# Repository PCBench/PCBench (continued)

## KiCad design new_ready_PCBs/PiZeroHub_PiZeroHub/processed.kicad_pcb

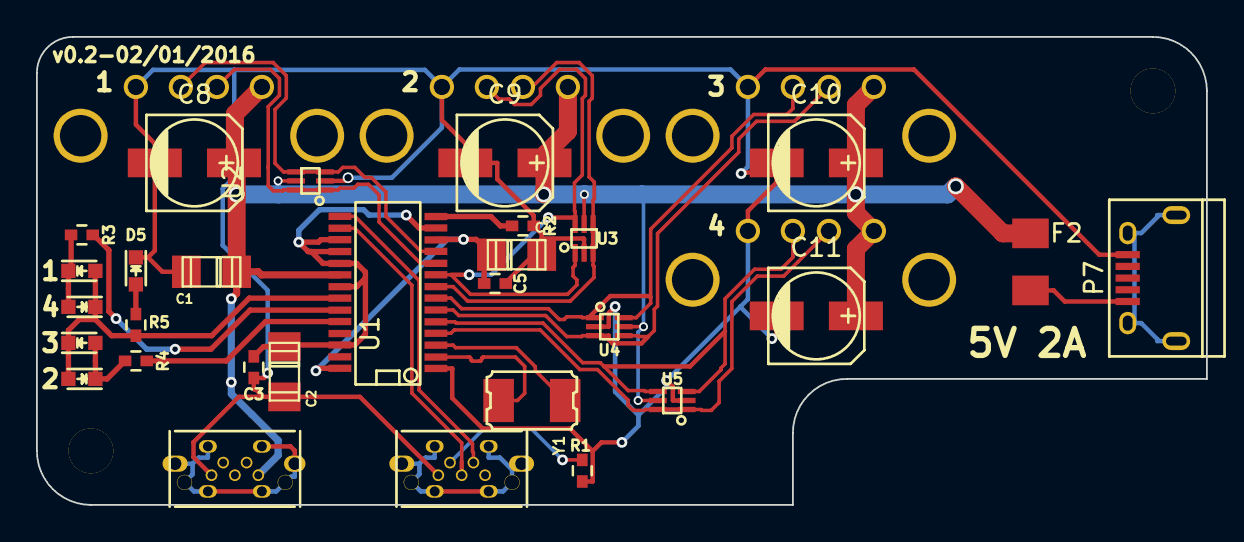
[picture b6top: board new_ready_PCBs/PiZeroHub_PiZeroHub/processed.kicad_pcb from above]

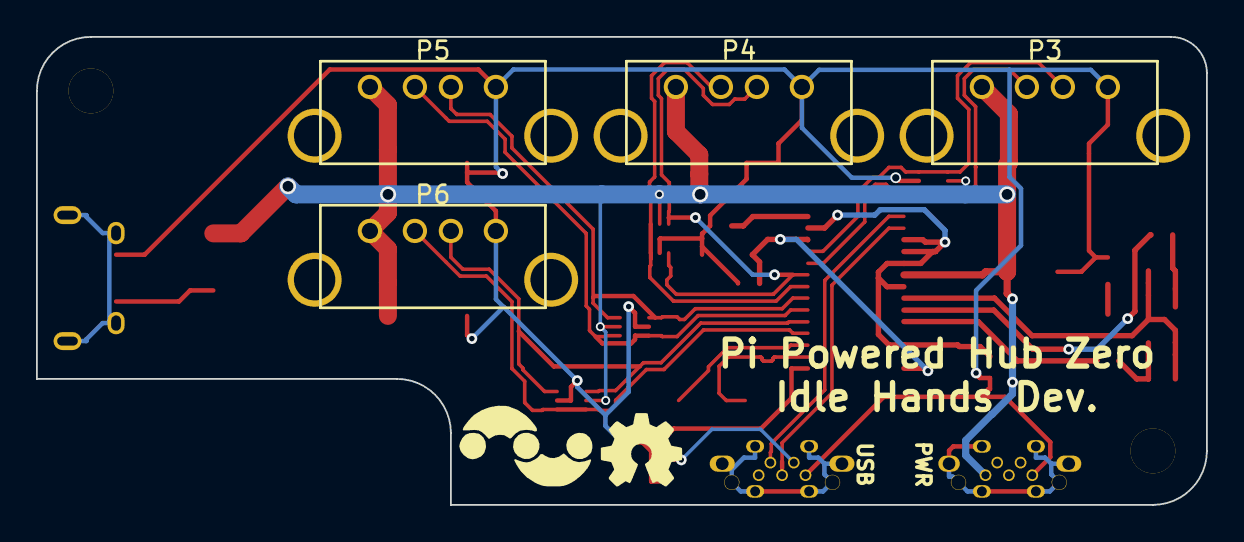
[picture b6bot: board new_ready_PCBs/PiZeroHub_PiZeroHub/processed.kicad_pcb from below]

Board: 2 copper layers, 65.0 x 26.0 mm, 33 parts (4 on the bottom side), 25 nets.

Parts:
C1, C2, C4: 10uF; c_1206_pol
C3, C5: 0.1uF; C_0402_Hand
C8, C9, C10, C11: 100uF; c_elec_5x5.3
D1, D2, D3, D4: Green; LED-0603
D5: Red; LED-0603
F2: 2A; Fuse_SMD1206_Wave
P1, P2: USB_OTG; USBOTG_BoardMount
P3, P4, P5, P6: USB_B; USB_A_Vert
P7: USB_POWER; USB_Micro-B
R1: 100k; R_0402_Hand
R2: 2.7k; R_0402_Hand
R3, R4, R5: 1k; R_0402_Hand
U1: FE1_1_4PORTUSB; SSOT28
U2, U3, U4, U5: USBLC6-2; SOT-666
Y1: Crystal_Small; crystal_smd_5x3.2mm

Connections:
+3V3: C2.1, C3.1, U1.13, U1.17, U1.18, U1.19, U1.21, U1.26
+5V: C1.1, C8.1, C9.1, C10.1, C11.1, F2.2, P1.1, P3.1, P4.1, P5.1, P6.1, U1.20, U2.5, U3.5, U4.5, U5.5
/D1+: P3.3, U1.11, U2.3, U2.4
/D1-: P3.2, U1.10, U2.1, U2.6
/D2+: P4.3, U1.9, U3.1, U3.6
/D2-: P4.2, U1.8, U3.3, U3.4
/D3+: P5.3, U1.7, U4.1, U4.6
/D3-: P5.2, U1.6, U4.3, U4.4
/D4+: P6.3, U1.5, U5.3, U5.4
/D4-: P6.2, U1.4, U5.1, U5.6
/X+: U1.3, Y1.2
/X-: U1.2, Y1.1
GND: C1.2, C2.2, C3.2, C4.2, C5.2, C8.2, C9.2, C10.2, C11.2, D5.1, P1.5, P2.5, P3.4, P4.4, P5.4, P6.4, P7.5, R1.1, R2.2, U1.1, U2.2, U3.2, U4.2, U5.2
unnamed: C4.1, C5.1, U1.12, U1.28
unnamed: D1.1, D2.2, R3.1
unnamed: D1.2, D2.1, D3.1, D4.2, R5.2, U1.22
unnamed: D3.2, D4.1, R4.1
unnamed: D5.2, R5.1
unnamed: F2.1, P7.1
unnamed: P2.2, U1.15
unnamed: P2.3, U1.16
unnamed: P2.4, R1.2
unnamed: R2.1, U1.14
unnamed: R3.2, U1.23
unnamed: R4.2, U1.24

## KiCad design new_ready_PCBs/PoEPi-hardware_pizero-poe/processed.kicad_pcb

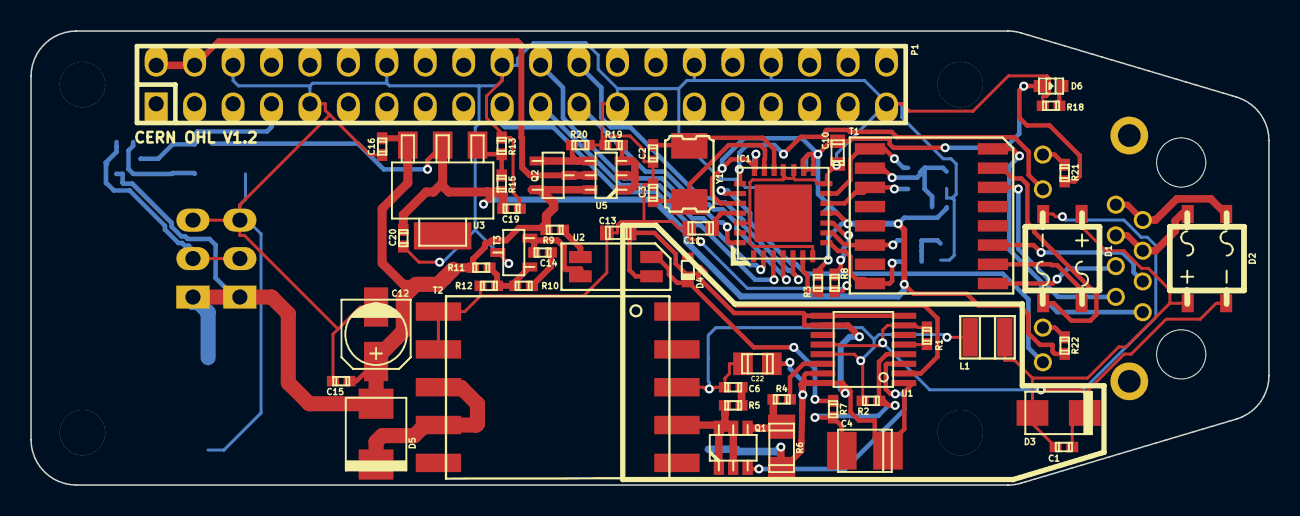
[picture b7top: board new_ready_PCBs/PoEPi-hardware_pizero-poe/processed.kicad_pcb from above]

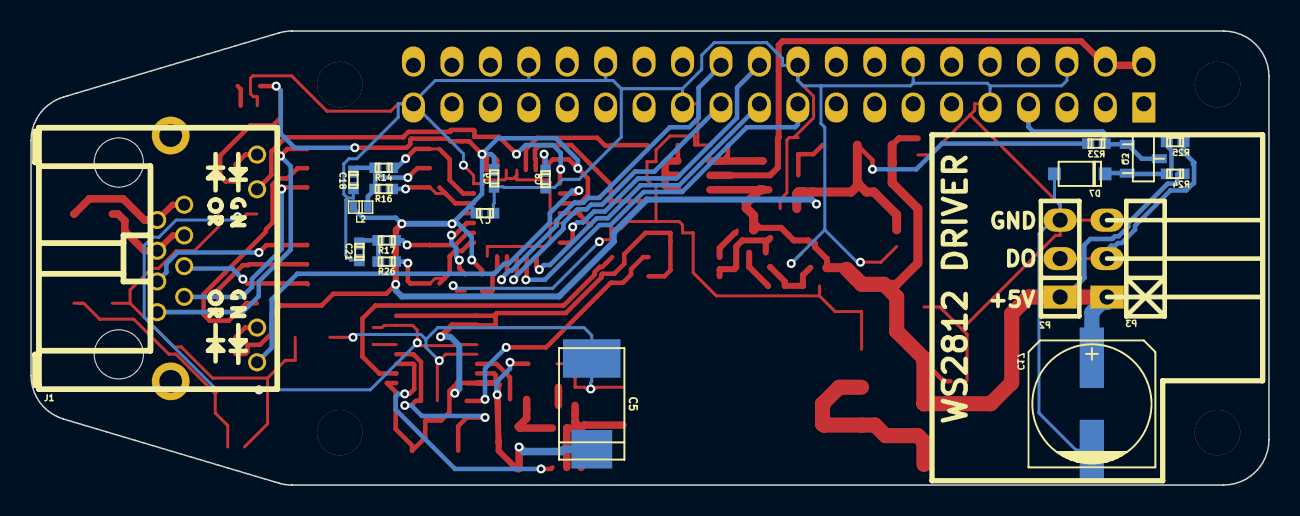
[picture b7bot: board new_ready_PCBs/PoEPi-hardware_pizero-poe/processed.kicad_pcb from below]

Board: 2 copper layers, 81.8 x 30.0 mm, 77 parts (20 on the bottom side), 57 nets.

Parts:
C1, C7, C8, C9, C18, C19, C21: 0.1uf; c_0402
C2, C3: 16pf; c_0402
C4: 220uf; c_tant_B
C5: 6.8uf; c_tant_D
C6, C14, C15, C16: C; c_0402
C10: 0.1uf; c_0603
C11: 10uf; c_0603
C12: CP; c_elec_4x4.5
C13: 2nf; c_0603
C17: CP; c_elec_8x6.5
C20: 1uf; c_0402
C22: 1uf; c_0805
D1, D2: BRIDGE; MBS
D3: ZENER; do214ac
D4: BAS516; sod523
D5: D_Schottky; do214aa
D6: LED; Led_0603
D7: ZENER; sod123
IC1: ENC28J60-I/ML; qfn-28
J1: RJ45-LED; rj45-tyco-2-406549-7
L1: 2.2uH; inductor_smd_1008
L2: BEAD; inductor_smd_0402
MT1, MT2, MT3, MT4: MountingHole_3mm
P1: Raspberry_Pi_+_Conn; pin_socket_20x2
P2: WS2812 Cn.; pin_strip_3
P3: WS2812 Cn.; pin_strip_3-90
Q1: SI3440DV; tsot-6
Q2, Q3: BSS138; sot23
R1: 68.1; r_0402
R2, R19: 10k; r_0402
R3: 1k; r_0402
R4, R5, R7, R9, R10, R11, R12: R; r_0402
R6: 0.05; r_1206
R8: 2.32k; r_0402
R13: 390; r_0402
R14, R16, R17, R26: 49.9; r_0402
R15: 240; r_0402
R18: 360; r_0402
R20: 47k; r_0402
R21, R22: 549; r_0402
R23, R24: 14k; r_0402
R25: 100; r_0402
T1: PULSE_H1197; H2019
T2: TRANSFO; PoE_TRANS
T3: VOLTAGE_REF; sot23
U1: LTC4267; ssop-16
U2: PAS291; OPTO_ISO
U3: LM1117IMPX-ADJ; sot223
U5: DMMT5401; sot23-6
Y1: 25Mhz; crystal_smd_5x3.2mm

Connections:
+3V3: C7.1, C8.1, C9.1, C10.1, C19.1, C20.1, D6.1, IC1.11, IC1.15, IC1.16, IC1.21, IC1.24, L2.2, R3.2, R15.1, R21.2, R22.2, R23.1, U3.2
+5V: C12.1, C15.1, C16.1, C17.1, D5.1, P2.1, P3.1, Q2.3, R9.1, R11.1, R24.1, U3.3, U5.6
/DATA_PAIR_1: D1.3, T1.10
/DATA_PAIR_2: D1.2, T1.15
/ENC_CS: IC1.5, P1.24
/ENC_INT: IC1.28, P1.22
/ENC_SCK: IC1.4, P1.23
/ENC_SI: IC1.3, P1.19
/ENC_SO: IC1.2, P1.21
/LEDA_CATH: IC1.23, J1.9
/LEDB_CATH: IC1.22, J1.11
/PVCC: C4.1, R2.2, R7.1, U1.4
/RUN: D4.2, R7.2, U2.4
/SPARE_PAIR_1: D2.3, J1.5, J1.6
/SPARE_PAIR_2: D2.2, J1.7, J1.8
/TPIN+: IC1.9, R17.2, T1.6
/TPIN-: IC1.8, R26.2, T1.8
/TPOUT+: IC1.13, R14.2, T1.1
/TPOUT-: IC1.12, R16.2, T1.3
/WS2812_DO: P1.7, Q3.1, Q3.2, R23.2
/sheet56B34F8B/5V_MCU: P1.2, P1.4, Q2.2, U5.5
GND: C2.1, C3.1, C7.2, C8.2, C9.2, C10.2, C11.1, C12.2, C13.1, C15.2, C16.2, C17.2, C18.1, C19.2, C20.2, C21.2, D7.1, IC1.7, IC1.14, IC1.17, IC1.18, IC1.26, P1.6, P1.9, P1.14, P1.20, P1.25, P1.30, P1.34, P1.39, P2.3, P3.3, R8.1, R12.2, R13.2, R18.2, R19.2, R20.2, T2.9, T2.10, T3.2
GNDPWR: C4.2, C5.2, C13.2, C22.2, R6.2, U1.1, U1.8, U1.9, U1.10, U1.15, U1.16, U2.3
unnamed: C1.1, D1.1, D2.1, D3.1, L1.1
unnamed: C1.2, D1.4, D2.4, D3.2, R1.2, U1.7, U1.12
unnamed: C2.2, IC1.19, Y1.1
unnamed: C3.2, IC1.20, Y1.2
unnamed: C6.2, R5.2
unnamed: C11.2, IC1.25
unnamed: C14.1, T3.3, U2.2
unnamed: C14.2, R10.2
unnamed: C18.2, L2.1, R14.1, R16.1, T1.2
unnamed: C21.1, R17.1, R26.1
unnamed: C5.1, C6.1, C22.1, L1.2, R2.1, T2.3, U1.13
unnamed: D4.1, U1.2
unnamed: D5.2, T2.7, T2.8
unnamed: D6.2, R18.1
unnamed: D7.2, Q3.3, R24.2, R25.2
unnamed: IC1.6, R3.1
unnamed: IC1.10, R8.2
unnamed: J1.1, T1.16
unnamed: J1.2, T1.14
unnamed: J1.3, T1.11
unnamed: J1.4, T1.9
unnamed: J1.10, R22.1
unnamed: J1.12, R21.1
unnamed: P2.2, P3.2, R25.1
unnamed: Q1.1, Q1.2, Q1.5, Q1.6, R5.1, T2.4
unnamed: Q1.3, U1.3
unnamed: Q1.4, R4.1, R6.1
unnamed: Q2.1, R20.1, U5.4
unnamed: R1.1, U1.5
unnamed: R4.2, U1.14
unnamed: R9.2, U2.1
unnamed: R10.1, R11.2, R12.1, T3.1
unnamed: R13.1, R15.2, U3.1
unnamed: R19.1, U5.1, U5.2, U5.3
